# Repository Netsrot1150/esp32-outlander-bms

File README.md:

# ESP32 Outlander BMS (v2)

Battery management firmware for an **ESP32-C3** that monitors **8 Mitsubishi Outlander PHEV battery modules (CMUs)** over CAN through an MCP2515, for a 64S lithium pack (~250 V).

**Status:** running in my VW Transporter (powering a big car audio system). Current version: **2.3.3**.

*The built-in web UI (shown here with `tools/mock_server.py`, no ESP32 needed).*

### Features
- Reads all 64 cell voltages, module temperatures and balancing status (4- and 8-cell CMUs)
- Automatic top balancing with safety conditions, plus manual mode
- State of charge, current/power/energy via a WCS1700 hall sensor
- Alarms, 24 h history and 14-day per-cell drift log (finds self-discharging cells)
- Web UI on its own Wi-Fi access point (works without home network), OTA firmware updates
- CAN recording and diagnostics export, ESP-NOW packets for a separate display
- Logic covered by 72 PC-side unit tests (`python tests/run_tests.py`)

### Credits
The CMU CAN protocol is based on public work by others:
- Tom de Bree – [OutlanderPHEVBMS](https://github.com/Tom-evnut/OutlanderPHEVBMS) (protocol and temperature calibration)
- knoxsp – [OutlanderCANManInTheMiddle](https://github.com/knoxsp/OutlanderCANManInTheMiddle) (CAN dumps from real modules)

The firmware itself was written from scratch, with AI assistance.

> ⚠️ This handles a high-voltage battery pack. Use at your own risk.

The documentation below is in Swedish.

---

## Om projektet (svenska)

Firmware som läser cellspänningar, temperaturer och balanseringsstatus från 8 Mitsubishi Outlander PHEV-CMU:er
via CAN (MCP2515), balanserar automatiskt, larmar och visar allt på en webbsida. Design: [`docs/`](docs/).

## Mappar

| Mapp | Innehåll |
|---|---|
| `BMS_v2/` | Firmwaren (Arduino-sketch) |
| `tests/` | PC-tester av logiken (`python tests/run_tests.py`) |
| `tools/` | `build.py` (kompilering), `mock_server.py` (förhandsvisa webbsidan) |

## Bygga

```bash
python tools/build.py
```

Resultat i `release/`:
- `BMS_v2-<version>-usb.bin` – första programmeringen via USB (adress 0x0). Raderar sparade inställningar.
- `BMS_v2-<version>-ota.bin` – uppdatering via webbsidan. Inställningarna behålls.

`python tools/build.py --sim` bygger en variant med 8 simulerade CMU:er för test utan batteri.

Kräver `BMS_v2/secrets.h` (kopiera `secrets.example.h` och fyll i eget WiFi-lösenord och hemnät).

## Programmera ESP:n första gången (USB, från laptopen)

1. Öppna https://espressif.github.io/esptool-js/ i Chrome eller Edge.
2. Anslut ESP32-C3 med USB, tryck **Connect** och välj porten.
   Om den inte hittas: håll **BOOT** intryckt, anslut USB, släpp BOOT.
3. Flash Address `0x0`, välj `BMS_v2-<version>-usb.bin`, tryck **Program**.
4. Tryck **RST** (eller dra ur och sätt i USB).

Alternativ: Arduino IDE med kortet **ESP32C3 Dev Module**, *USB CDC On Boot: Enabled* och
*Partition Scheme: Minimal SPIFFS (1.9MB APP with OTA/190KB SPIFFS)*. Bibliotek: ESPAsyncWebServer 3.9.x,
AsyncTCP 3.4.x och ArduinoJson 7.x.

## Använda

- Anslut till WiFi **BMS-Transporter** (lösenordet står i `secrets.h`) och öppna http://192.168.4.1
- Hemma (om hemnätet är inställt): http://bms.local eller den fasta IP du valt
- Uppdatera firmware: Diagnostik → Firmware-uppdatering → välj `-ota.bin`.
- Glömt lösenordet: håll **BOOT** intryckt i 5 s medan BMS:en är igång. Nätverksinställningarna återställs.

## Strömsensor (WCS1700)

Koppling: VCC → 3,3 V, GND → GND, AO → GPIO3. DO lämnas oansluten.
Dra **en** ledare genom sensorn (inte + och − tillsammans). Vänd sensorn så att urladdning ger sjunkande
spänning på AO, eller kryssa i "Vänd strömriktningen".

1. Inställningar → Ström och laddnivå → kryssa i "Strömsensor ansluten" → Spara.
2. Med laddare och last avstängda: "Nolla ström nu".
3. Starta laddaren och jämför BMS:ens ström med laddarens. Justera "Känslighet" om de skiljer sig.

Laddnivån räknas från lägsta cellen (3,30 V = 0 %, 4,10 V = 100 %) och visas som **andel av energin**
(från v2.3). Spänningskurvan gäller GS Yuasa LEV46 (46 Ah, 2,75–4,10 V) och ligger i `BMS_v2/soc.cpp`
med källor; kWh kvar räknas med samma kurva. Ah-räkningen sker i laddning och räknas om till energi
för visning. Laddningsprocenten syns om man håller muspekaren över procenttalet. Utan sensor: från vilospänningen
("uppskattad"). Med sensor: Ah-räkning som rättas till 100 % när laddaren slutat och mot vilospänningen
efter 30 min vila.

Grafer: fliken Grafer visar 10 min (1 s upplösning) och 1 h/6 h/24 h (1 min, sparas i flash).

## Cellogg och utjämning (v2.2)

- Cellspänningarna jämnas ut med en tidskonstant på ca 4 s (100 ramar vid 25 Hz). Rådata syns i
  Diagnostik → Rå CAN. Min/max-platsen byter cell först när den nya är minst 0,5 mV lägre/högre.
- Celloggen sparar timmedel för alla 64 celler i 14 dygn (`/cells.bin`, 24 kB). Grafen under Grafer
  visar avvikelsen från medianen; de 5 lägsta och 5 högsta är färgade och tabellen visar drift i
  mV/dygn. En cell som tappar mer än ca 3 mV/dygn vid vila självurladdar troligen.
- MCP2515 filtrerar bort 0x6X4, 0x6X5 och alla icke-CMU-ramar (utom under CAN-inspelning). CAN-varningen
  kräver > 50 overflow per 10 s och ligger kvar 30 s.
- Diagnostik → System visar orsaken till senaste omstart (strömpåslag, OTA, brownout, krasch …).

## Kontroll på riktig hårdvara

Skicka resultatet (och filerna från punkt 4) för analys:

1. Programmera via USB enligt ovan.
2. Anslut till `BMS-Transporter` och öppna 192.168.4.1. Fungerar det helt utan hemnätet?
3. Diagnostik: syns alla 8 CMU-id? Hur många ramar/s per CMU vid 200 ms pollintervall? Ändras det om
   pollintervallet sätts till 100 eller 500 ms? Hur många RX-overflow?
4. Tryck **Spela in CAN 10 s**, ladda ner **CSV** och **rapport**.
5. Temperatur: jämför rådata (Diagnostik, sub 1, byte 2–7) med IR-mätning på modulen och ställ in förskjutningen.
6. Hemma: nås bms.local (och den fasta IP:n), och fungerar BMS-Transporter samtidigt?
7. Balansering: läge Manuell, mål strax under högsta cell. Bara celler över målet ska få bleed (randig stapel).
   Läge Av ska släppa alla.
8. OTA: ladda upp en `-ota.bin` via webbsidan.

## Utveckling

```bash
python tests/run_tests.py
```

```bash
python tools/mock_server.py
```

Mock-servern läser sidan direkt ur `BMS_v2/web_ui.h` och simulerar API:t på http://localhost:8080.

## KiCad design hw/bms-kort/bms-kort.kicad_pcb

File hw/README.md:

# BMS-kort rev A

Bärkort för ESP32-C3 SuperMini med alltid-på-matning, brytbar CMU-matning, 12 V-mätning och CAN via
C3:ans inbyggda TWAI. Design och beslut: `docs/design-bms-kort.md`.

## Vad kortet gör

- **12 V in (J1)** från det separata AGM-batteriet, med skydd mot omvänd polaritet (Q1) och spikar (D1).
- **5 V till ESP:n, alltid på** (TPS560430X, ca 80 µA i vila). Omvandlaren startar vid 11,5 V och stänger
  av under ca 10,3 V, så kortet kan aldrig djupladda batteriet ens om firmwaren hänger sig.
- **BMS-skena (J2 + CAN + strömsensor)** som ESP:n slår på med GPIO10. Den är av vid start, vid krasch och i
  djupsömn. Grön lysdiod (D3) visar att den är på. Polyfuse 2 A och frihjulsdiod på CMU-utgången.
- **CAN (J3)** med SN65HVD230 på TWAI, ESD-skydd och 120 Ω avslutning med bygel (JP1).
- **12 V-mätning** på GPIO1 (15 V -> 2,5 V) och **WCS1700 (J4)** på GPIO0.
- **Sömnström** ca 0,13 mA från 12 V när SuperMini:s ström-LED är borttagen (ca 0,1 Ah per månad).
- Monteringshålen är opläterade: HV-sidans 12 V är isolerad från karossen och får inte jordas via skruvarna.

| Kontakt | Stift |
|---|---|
| J1 12 V in | +12V, GND |
| J2 CMU 12 V ut | +12V (bryts), GND |
| J3 CAN | GND, CANL, CANH |
| J4 WCS1700 | 3,3 V (bryts), GND, AO |
| J5 expansion (ej monterad) | 3V3, GND, IO6, IO7, IO20 |
| JP1 | bygel på = 120 Ω |

## Filer

| Fil | Innehåll |
|---|---|
| `bms-kort/` | KiCad 10-projekt (schema, kort, egna bibliotek via `../lib`) |
| `fab/bms-kort-gerber.zip` | Gerber och borrfiler |
| `fab/bms-kort-bom.csv`, `fab/bms-kort-cpl.csv` | BOM och placering i JLC:s format |
| `fab/handlodning.csv` | Hålmonterade delar att löda själv |
| `fab/bms-kort-schema.pdf`, `fab/render_*.png` | Schema och bilder |
| `gen/` | Skripten som genererar allt ur `gen/circuit.py` (kretsen) och `gen/layout.py` (placeringen) |

## Generera om

```bash
python hw/gen/library.py
```

```bash
F:/KiCad/bin/python.exe hw/gen/pcb_build.py
```

```bash
F:/KiCad/bin/python.exe hw/gen/route.py
```

```bash
python hw/gen/sch.py
```

```bash
python hw/gen/fab.py
```

`route.py` använder Freerouting 2.x (miljövariabeln `FREEROUTING_JAR` eller `hw/tools/freerouting.jar`, ingår
inte i repot) och slutar med DRC. Allt ska ge 0 fel.

## Beställa hos JLCPCB

1. Ladda upp `fab/bms-kort-gerber.zip`. 2 lager, 1,6 mm, 74 x 56 mm, valfri färg, HASL eller ENIG.
2. Kryssa i **PCB Assembly**, Economic, Top side.
3. Ladda upp `fab/bms-kort-bom.csv` och `fab/bms-kort-cpl.csv`.
4. Kontrollera rotationen i JLC:s förhandsgranskning, särskilt Q1–Q3 och D4 (SOT-23), U2 (SOT-89), U3
   (SOIC-8, punkten vid stift 1), D1, D2, D5 (bandet mot katoden) och D3 (lysdiodens katod mot GND).
5. Sex extended-delar (U1, U2, L1, F1, D1, D4) kostar ca 3 USD var i uppstartsavgift. Resten är basic-delar.

Handlödda delar (`fab/handlodning.csv`): J1, J2 (KF2EDGR-5.08-2P), J3 (15EDGRC-3.5-03P), J4 (B3B-XH-A),
JP1 med bygel och två hylslister 1x8 (C27438) för SuperMini. Beställ pluggarna samtidigt:
2 st KF2EDGK-5.08-2P (C440880) och 1 st 15EDGK-3.5-03P (C5188250).

## Före beställning

1. Mät radavståndet på ditt SuperMini: 15,24 mm. Pinnordningen på kortet (sett ovanifrån, USB-C åt höger):
   nedre raden 0, 1, 2, 3, 4, 3V3, G, 5V och övre raden 21, 20, 10, 9, 8, 7, 6, 5.
2. Kontrollera WCS1700-modulens stiftordning mot J4 (3,3 V, GND, AO).

## Första start

1. Ta bort den röda ström-LED:en på SuperMini (eller låt den sitta och räkna med ca 1–3 mA mer).
2. Utan SuperMini: anslut 12 V via labbagg med strömbegränsning 100 mA. Mät 4,9 V på mätpunkten 5V och
   ca 12 V på VIN. Strömmen ska vara under 0,2 mA.
3. Sänk spänningen: 5 V ska försvinna under ca 10,3 V och komma tillbaka över ca 11,5 V.
4. Sätt i SuperMini och flasha firmware med kortstöd (kommer i nästa version). Kontrollera att den gröna
   lysdioden tänds när firmwaren slår på BMS-skenan och att CMU:erna syns.

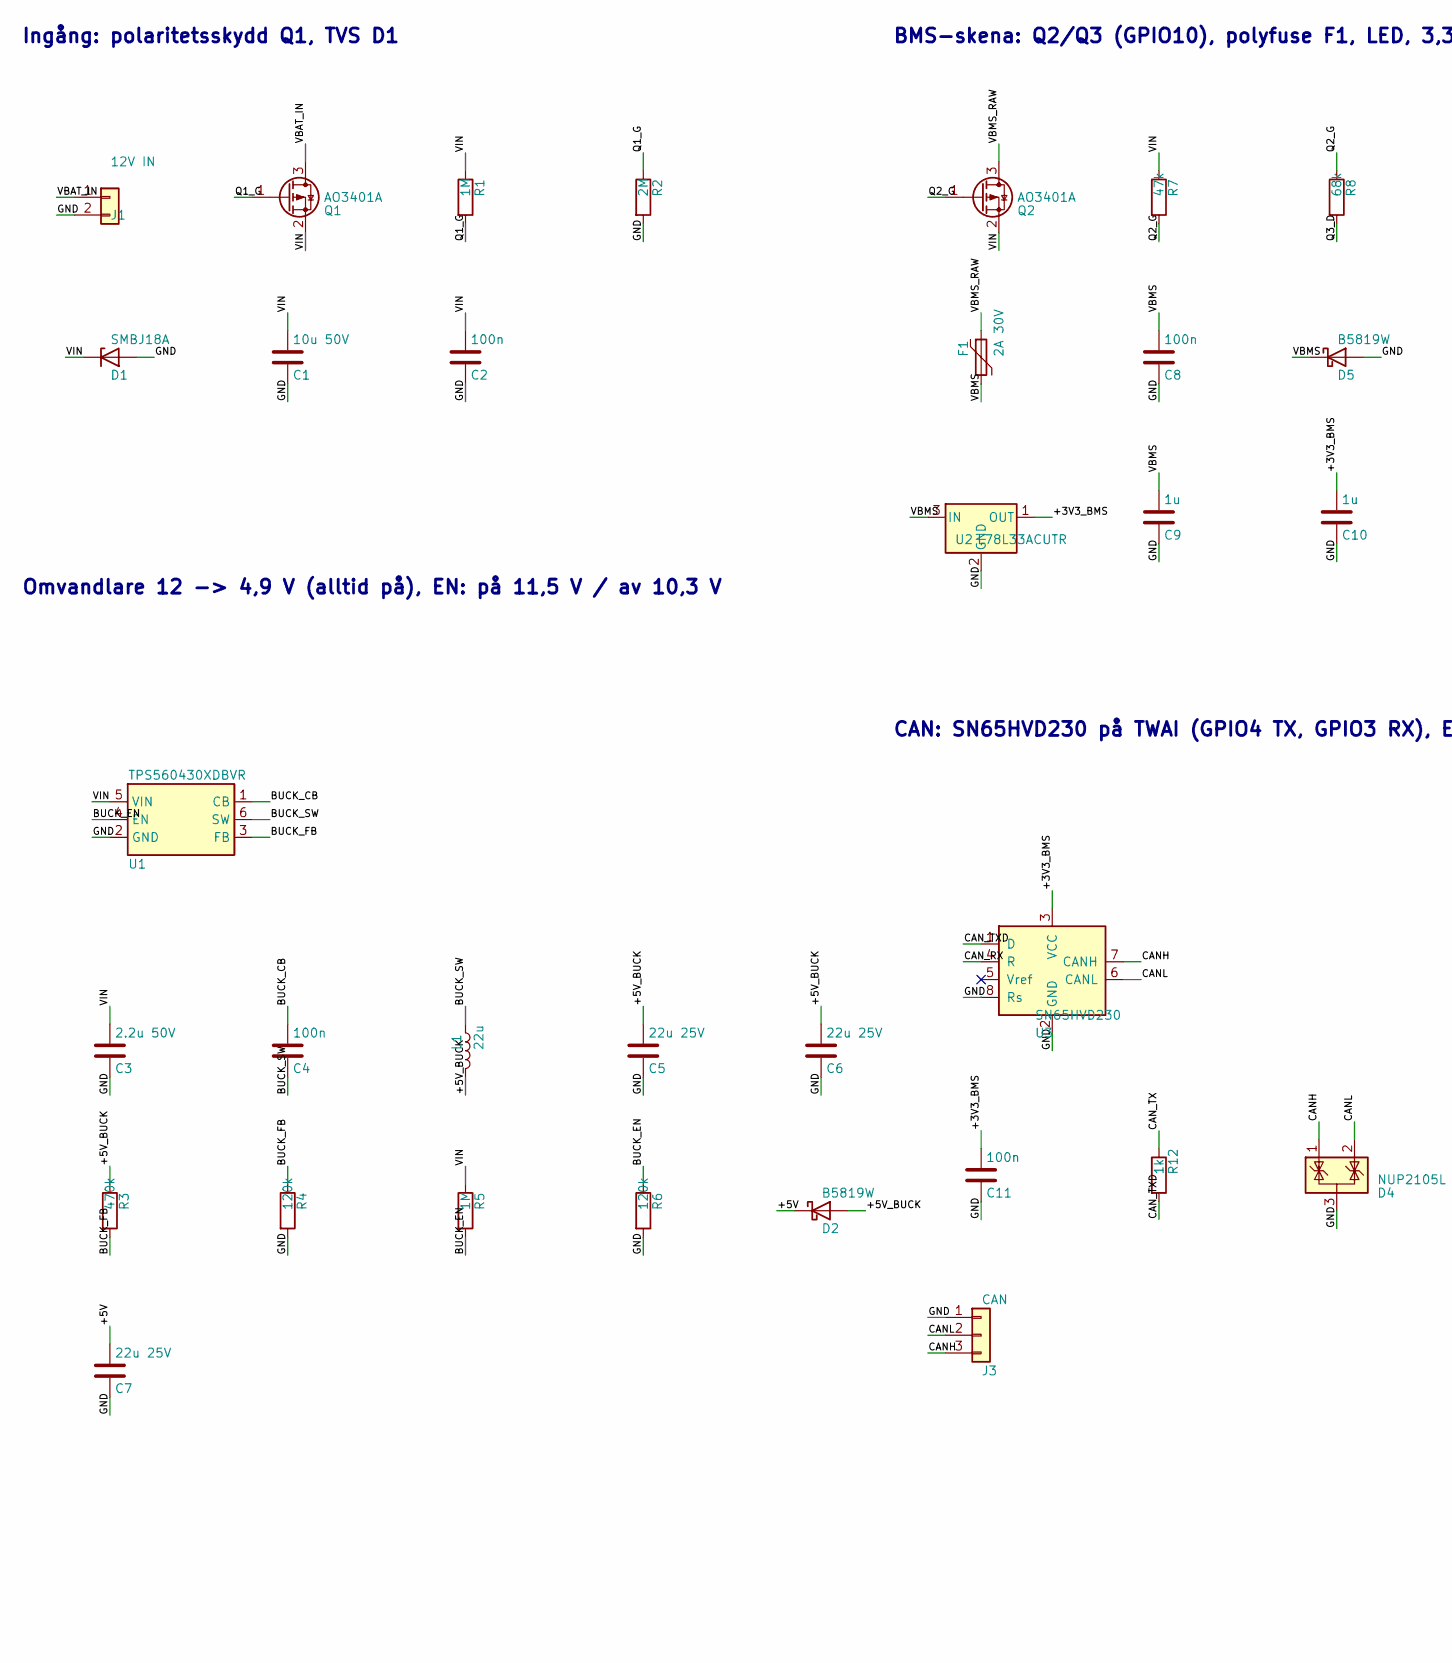
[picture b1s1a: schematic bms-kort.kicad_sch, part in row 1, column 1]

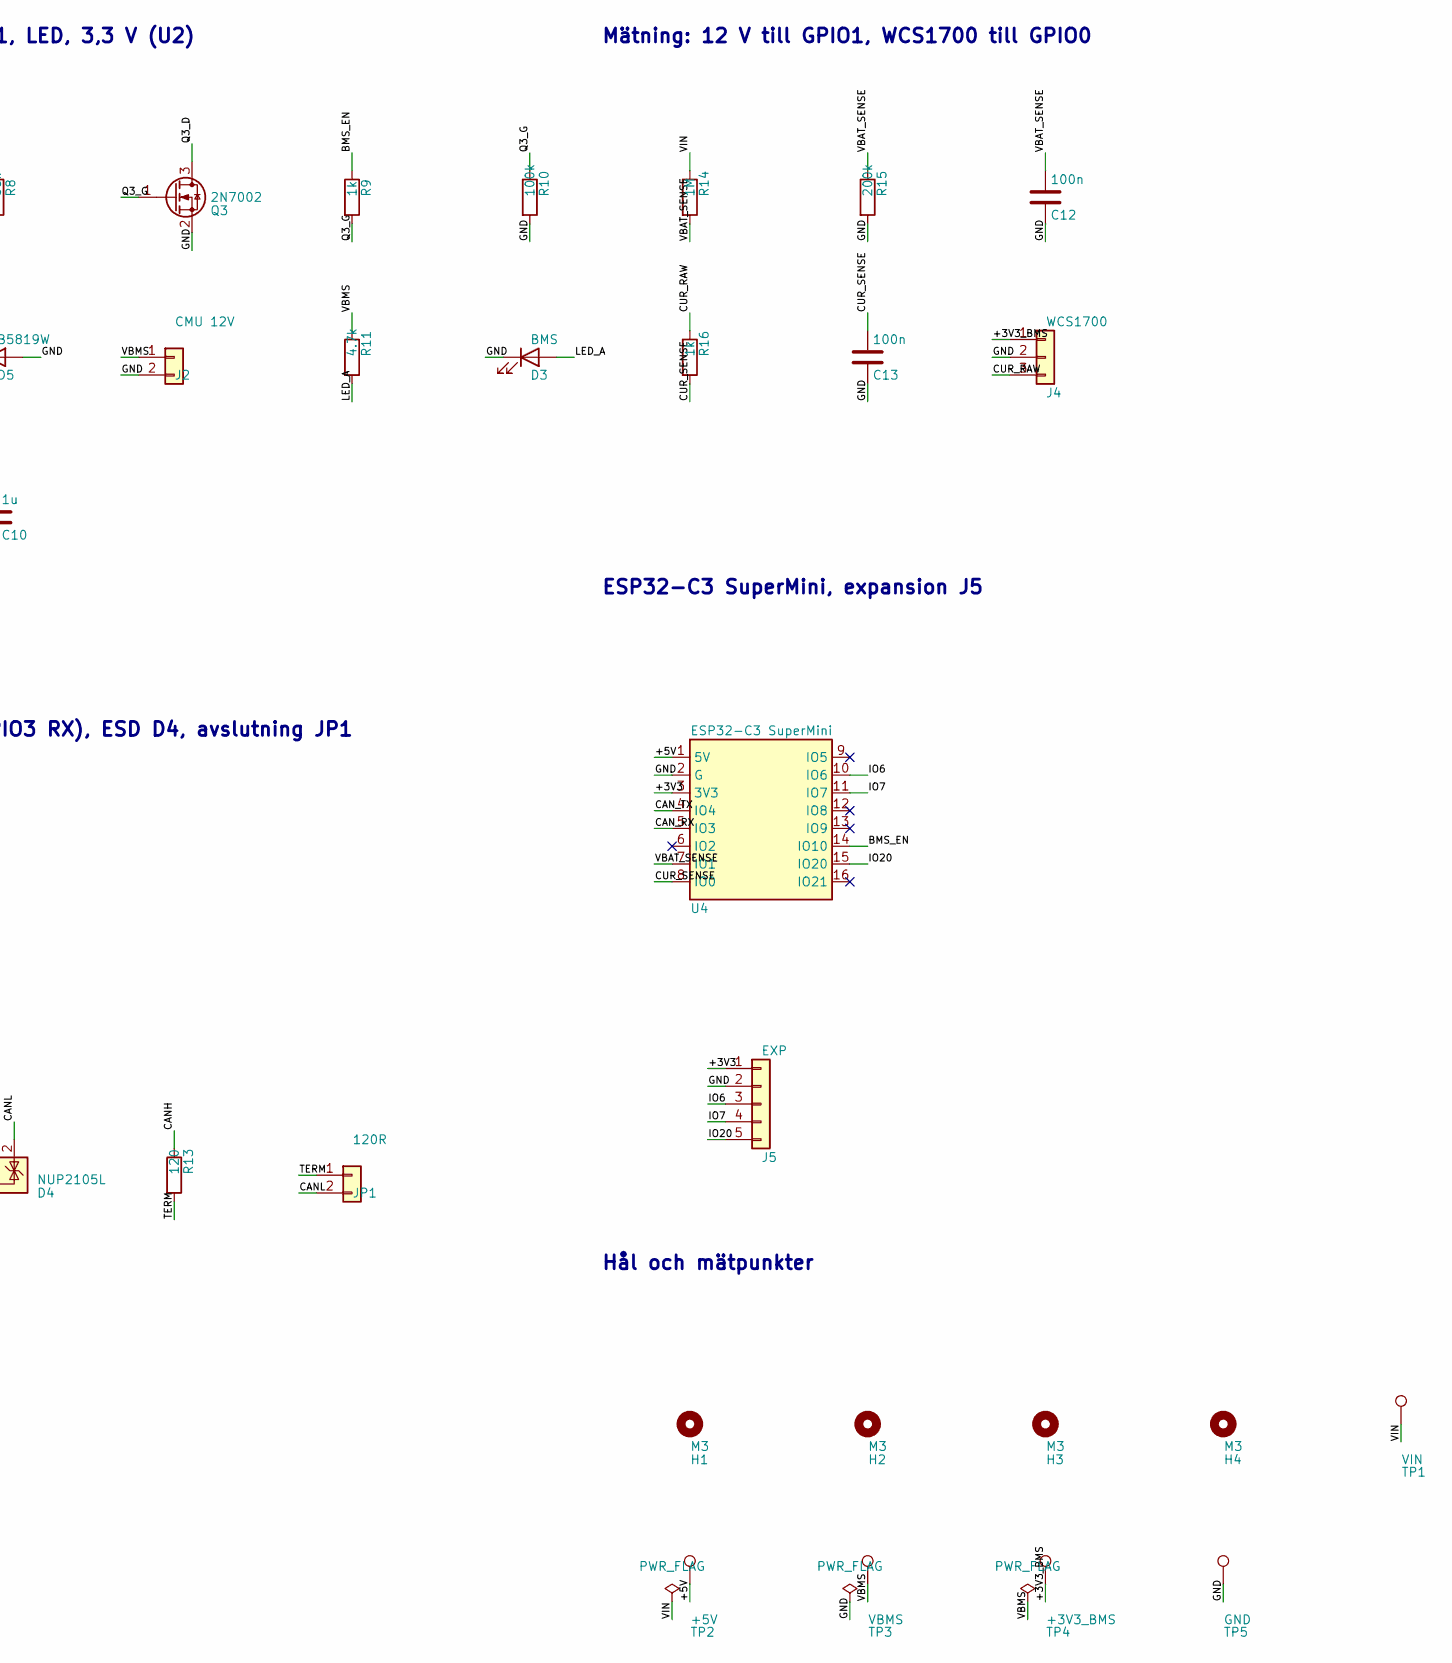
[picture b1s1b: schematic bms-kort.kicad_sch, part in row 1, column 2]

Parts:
C1: 10u 50V; C_1206_3216Metric; LCSC C13585
C2, C4, C8, C11, C12, C13: 100n; C_0603_1608Metric; LCSC C14663
C3: 2.2u 50V; C_1206_3216Metric; LCSC C50254
C5, C6, C7: 22u 25V; C_0805_2012Metric; LCSC C45783
C9, C10: 1u; C_0603_1608Metric; LCSC C15849
D1: SMBJ18A; D_SMB; LCSC C353379
D2, D5: B5819W; D_SOD-123; LCSC C8598
D3: BMS; LED_0805_2012Metric; LCSC C2297
D4: NUP2105L; SOT-23; LCSC C14486
F1: 2A 30V; Fuse_1812_4532Metric; LCSC C18198342
H1, H2, H3, H4: M3; MountingHole_3.2mm_M3
J1: 12V IN; PhoenixContact_MSTBA_2,5_2-G-5,08_1x02_P5.08mm_Horizontal; LCSC C441204
J2: CMU 12V; PhoenixContact_MSTBA_2,5_2-G-5,08_1x02_P5.08mm_Horizontal; LCSC C441204
J3: CAN; PhoenixContact_MC_1,5_3-G-3.5_1x03_P3.50mm_Horizontal; LCSC C5160226
J4: WCS1700; JST_XH_B3B-XH-A_1x03_P2.50mm_Vertical; LCSC C144394
J5: EXP; PinHeader_1x05_P2.54mm_Vertical
JP1: 120R; PinHeader_1x02_P2.54mm_Vertical; LCSC C492401
L1: 22u; L_Sunlord_SWPA5040S; LCSC C68434
Q1, Q2: AO3401A; SOT-23; LCSC C15127
Q3: 2N7002; SOT-23; LCSC C8545
R1, R5, R14: 1M; R_0603_1608Metric; LCSC C22935
R2: 2M; R_0603_1608Metric; LCSC C22976
R3: 470k; R_0603_1608Metric; LCSC C23178
R4, R6: 120k; R_0603_1608Metric; LCSC C25808
R7: 47k; R_0603_1608Metric; LCSC C25819
R8: 68k; R_0603_1608Metric; LCSC C23231
R9, R12, R16: 1k; R_0603_1608Metric; LCSC C21190
R10: 100k; R_0603_1608Metric; LCSC C25803
R11: 4.7k; R_0603_1608Metric; LCSC C23162
R13: 120; R_0603_1608Metric; LCSC C22787
R15: 200k; R_0603_1608Metric; LCSC C25811
TP1: VIN; TestPoint_Pad_D1.5mm
TP2: +5V; TestPoint_Pad_D1.5mm
TP3: VBMS; TestPoint_Pad_D1.5mm
TP4: +3V3_BMS; TestPoint_Pad_D1.5mm
TP5: GND; TestPoint_Pad_D1.5mm
U1: TPS560430XDBVR; SOT-23-6; LCSC C524782
U2: L78L33ACUTR; SOT-89-3; LCSC C14170
U3: SN65HVD230; SOIC-8_3.9x4.9mm_P1.27mm; LCSC C12084
U4: ESP32-C3 SuperMini; ESP32C3_SuperMini_Socket; LCSC C27438

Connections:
+3V3: J5.1, U4.3 (3V3)
+3V3_BMS: C10.1, C11.1, J4.1, TP4.1, U2.1 (OUT), U3.3 (VCC)
+5V: C7.1, D2.1 (K), TP2.1, U4.1 (5V)
+5V_BUCK: C5.1, C6.1, D2.2 (A), L1.2, R3.1
BMS_EN: R9.1, U4.14 (IO10)
BUCK_CB: C4.1, U1.1 (CB)
BUCK_EN: R5.2, R6.1, U1.4 (EN)
BUCK_FB: R3.2, R4.1, U1.3 (FB)
BUCK_SW: C4.2, L1.1, U1.6 (SW)
CANH: D4.1 (K), J3.3, R13.1, U3.7 (CANH)
CANL: D4.2 (K), J3.2, JP1.2, U3.6 (CANL)
CAN_RX: U3.4 (R), U4.5 (IO3)
CAN_TX: R12.1, U4.4 (IO4)
CAN_TXD: R12.2, U3.1 (D)
CUR_RAW: J4.3, R16.1
CUR_SENSE: C13.1, R16.2, U4.8 (IO0)
GND: C1.2, C2.2, C3.2, C5.2, C6.2, C7.2, C8.2, C9.2, C10.2, C11.2, C12.2, C13.2, D1.2 (A), D3.1 (K), D4.3 (A), D5.2 (A), J1.2, J2.2, J3.1, J4.2, J5.2, Q3.2 (S), R2.2, R4.2, R6.2, R10.2, R15.2, TP5.1, U1.2 (GND), U2.2 (GND), U3.2 (GND), U3.8 (Rs), U4.2 (G)
IO6: J5.3, U4.10 (IO6)
IO7: J5.4, U4.11 (IO7)
IO20: J5.5, U4.15 (IO20)
LED_A: D3.2 (A), R11.2
Q1_G: Q1.1 (G), R1.2, R2.1
Q2_G: Q2.1 (G), R7.2, R8.1
Q3_D: Q3.3 (D), R8.2
Q3_G: Q3.1 (G), R9.2, R10.1
TERM: JP1.1, R13.2
VBAT_IN: J1.1, Q1.3 (D)
VBAT_SENSE: C12.1, R14.2, R15.1, U4.7 (IO1)
VBMS: C8.1, C9.1, D5.1 (K), F1.2, J2.1, R11.1, TP3.1, U2.3 (IN)
VBMS_RAW: F1.1, Q2.3 (D)
VIN: C1.1, C2.1, C3.1, D1.1 (K), Q1.2 (S), Q2.2 (S), R1.1, R5.1, R7.1, R14.1, TP1.1, U1.5 (VIN)

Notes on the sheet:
Ingång: polaritetsskydd Q1, TVS D1
Omvandlare 12 -> 4,9 V (alltid på), EN: på 11,5 V / av 10,3 V
BMS-skena: Q2/Q3 (GPIO10), polyfuse F1, LED, 3,3 V (U2)
CAN: SN65HVD230 på TWAI (GPIO4 TX, GPIO3 RX), ESD D4, avslutning JP1
Mätning: 12 V till GPIO1, WCS1700 till GPIO0
ESP32-C3 SuperMini, expansion J5
Hål och mätpunkter

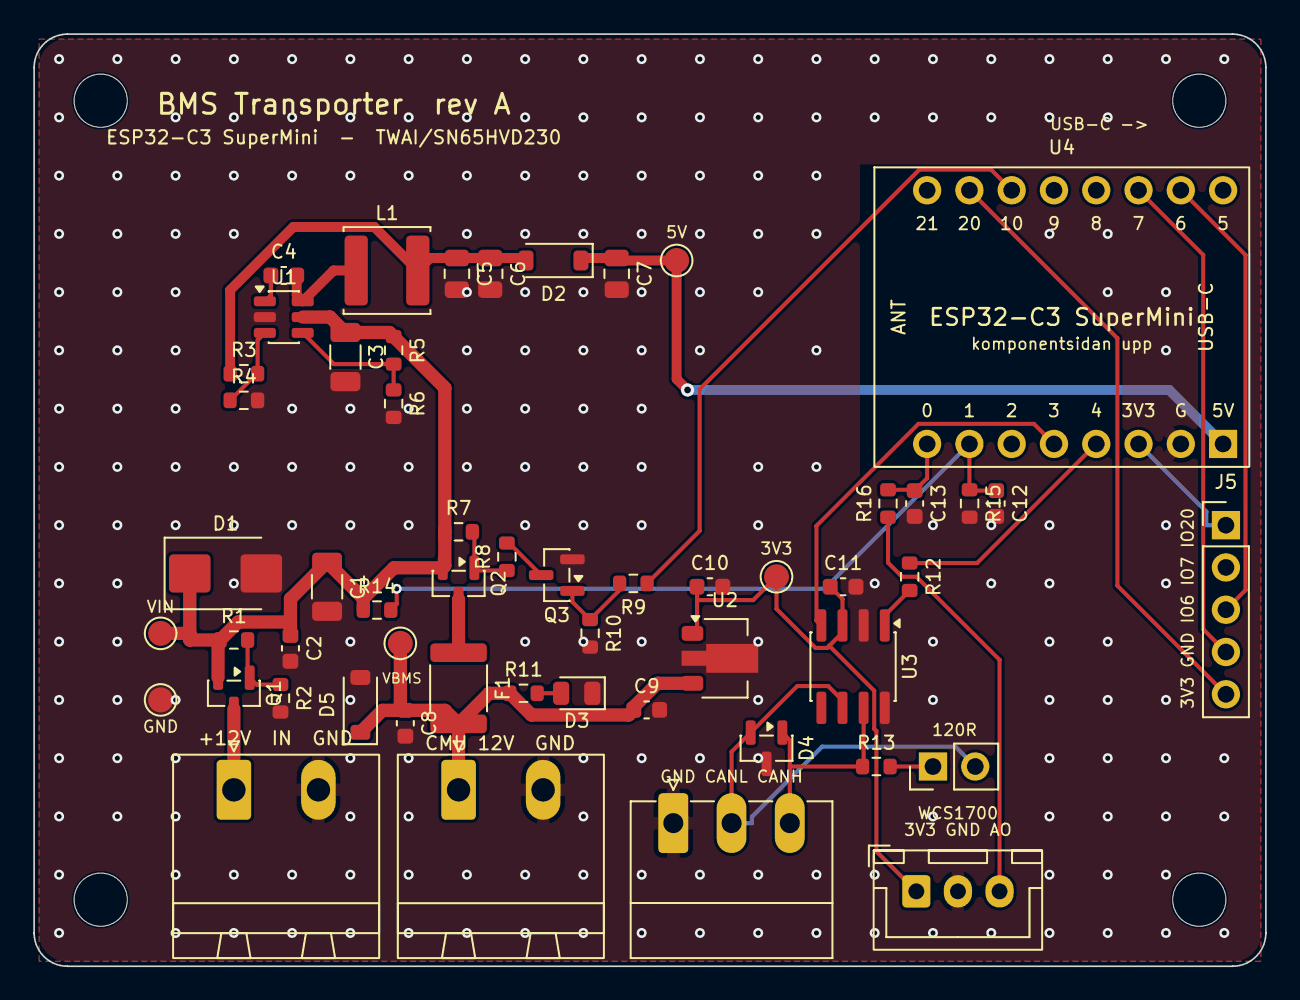
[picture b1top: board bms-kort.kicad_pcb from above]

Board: 2 copper layers, 74.0 x 56.0 mm, 58 parts (0 on the bottom side), 31 nets.

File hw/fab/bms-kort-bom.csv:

Comment,Designator,Footprint,LCSC
SN65HVD230,U3,SOIC-8_3.9x4.9mm_P1.27mm,C12084
10u 50V,C1,C_1206_3216Metric,C13585
L78L33ACUTR,U2,SOT-89-3,C14170
NUP2105L,D4,SOT-23,C14486
100n,"C2,C4,C8,C11,C12,C13",C_0603_1608Metric,C14663
AO3401A,"Q1,Q2",SOT-23,C15127
1u,"C9,C10",C_0603_1608Metric,C15849
2A 30V,F1,Fuse_1812_4532Metric,C18198342
1k,"R9,R12,R16",R_0603_1608Metric,C21190
120,R13,R_0603_1608Metric,C22787
1M,"R1,R5,R14",R_0603_1608Metric,C22935
BMS,D3,LED_0805_2012Metric,C2297
2M,R2,R_0603_1608Metric,C22976
4.7k,R11,R_0603_1608Metric,C23162
470k,R3,R_0603_1608Metric,C23178
68k,R8,R_0603_1608Metric,C23231
100k,R10,R_0603_1608Metric,C25803
120k,"R4,R6",R_0603_1608Metric,C25808
200k,R15,R_0603_1608Metric,C25811
47k,R7,R_0603_1608Metric,C25819
SMBJ18A,D1,D_SMB,C353379
22u 25V,"C5,C6,C7",C_0805_2012Metric,C45783
2.2u 50V,C3,C_1206_3216Metric,C50254
TPS560430XDBVR,U1,SOT-23-6,C524782
22u,L1,L_Sunlord_SWPA5040S,C68434
2N7002,Q3,SOT-23,C8545
B5819W,"D2,D5",D_SOD-123,C8598
